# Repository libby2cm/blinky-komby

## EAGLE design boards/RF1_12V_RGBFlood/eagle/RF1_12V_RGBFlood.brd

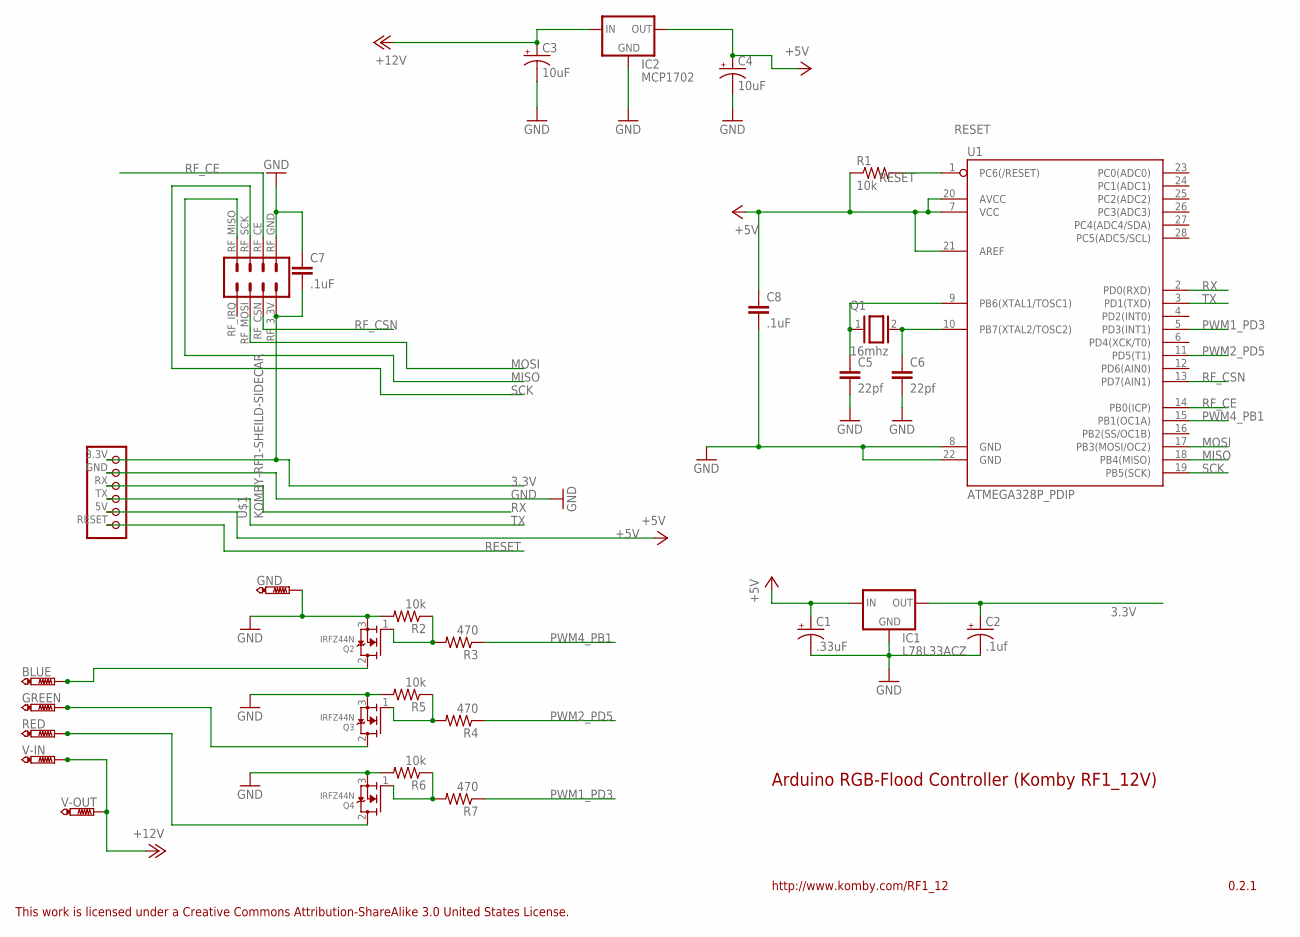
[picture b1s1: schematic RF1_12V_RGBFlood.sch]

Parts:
BLUE: PTR1PAD1-13Y; P1-13Y
C1: .33uF; E1,8-4
C2: .1uf; E1,8-4
C3, C4: 10uF; E1,8-4
C5, C6: 22pf; C025-024X044
C7, C8: .1uF; C025-024X044
GND: PTR1PAD1-13Y; P1-13Y
GREEN: PTR1PAD1-13Y; P1-13Y
IC1: L78L33ACZ; 78LXX
IC2: MCP1702; TO92
Q1: 16mhz; QS
Q2, Q3, Q4: IRFZ44N; TO220V
R1, R2, R5, R6: 10k; 0207/7
R3, R4, R7: 470; 0207/7
RED: PTR1PAD1-13Y; P1-13Y
U1: ATMEGA328P_PDIP; DIL28-3
U$1: KOMBY-RF1-SHEILD-SIDECAR; KOMBY-RF1-SIDECAR
V-IN: PTR1PAD1-13Y; P1-13Y
V-OUT: PTR1PAD1-13Y; P1-13Y

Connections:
3.3V: C2.+, C7.2, IC1.OUT, U$1.3.3V, U$1.RF_3.3V
+5V: C1.+, C4.+, C8.1, IC1.IN, IC2.3 (OUT), R1.1, U1.7 (VCC), U1.20 (AVCC), U1.21 (AREF), U$1.5V
+12V: C3.+, IC2.2 (IN), V-IN.TP, V-OUT.TP
GND: C1.-, C2.-, C3.-, C4.-, C5.2, C6.2, C7.1, C8.2, GND.TP, IC1.GND, IC2.1 (GND), Q2.3 (S), Q3.3 (S), Q4.3 (S), R2.2, R5.2, R6.2, U1.8 (GND), U1.22 (GND), U$1.GND, U$1.RF_GND (RFGND_1)
MISO: U1.18 (PB4(MISO)), U$1.RF_MISO
MOSI: U1.17 (PB3(MOSI/OC2)), U$1.RF_MOSI
unnamed: C6.1, Q1.2, U1.10 (PB7(XTAL2/TOSC2))
unnamed: C5.1, Q1.1, U1.9 (PB6(XTAL1/TOSC1))
PWM1_PD3: R7.1, U1.5 (PD3(INT1))
PWM2_PD5: R4.1, U1.11 (PD5(T1))
PWM4_PB1: R3.1, U1.15 (PB1(OC1A))
RESET: R1.2, U1.1 (PC6(/RESET)), U$1.RESET
RF_CE: U1.14 (PB0(ICP)), U$1.RF_CE
RF_CSN: U1.13 (PD7(AIN1)), U$1.RF_CSN
RGB_N$1: Q2.1 (G), R2.1, R3.2
RGB_N$2: Q3.1 (G), R4.2, R5.1
RGB_N$3: Q4.1 (G), R6.1, R7.2
RGB_N$4: Q4.2 (D), RED.TP
RGB_N$7: GREEN.TP, Q3.2 (D)
RGB_N$8: BLUE.TP, Q2.2 (D)
RX: U1.2 (PD0(RXD)), U$1.RX
SCK: U1.19 (PB5(SCK)), U$1.RF_SCK
TX: U1.3 (PD1(TXD)), U$1.TX

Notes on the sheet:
Arduino RGB-Flood Controller (Komby RF1_12V)
0.2.1
http://www.komby.com/RF1_12
This work is licensed under a Creative Commons Attribution-ShareAlike 3.0 United States License.

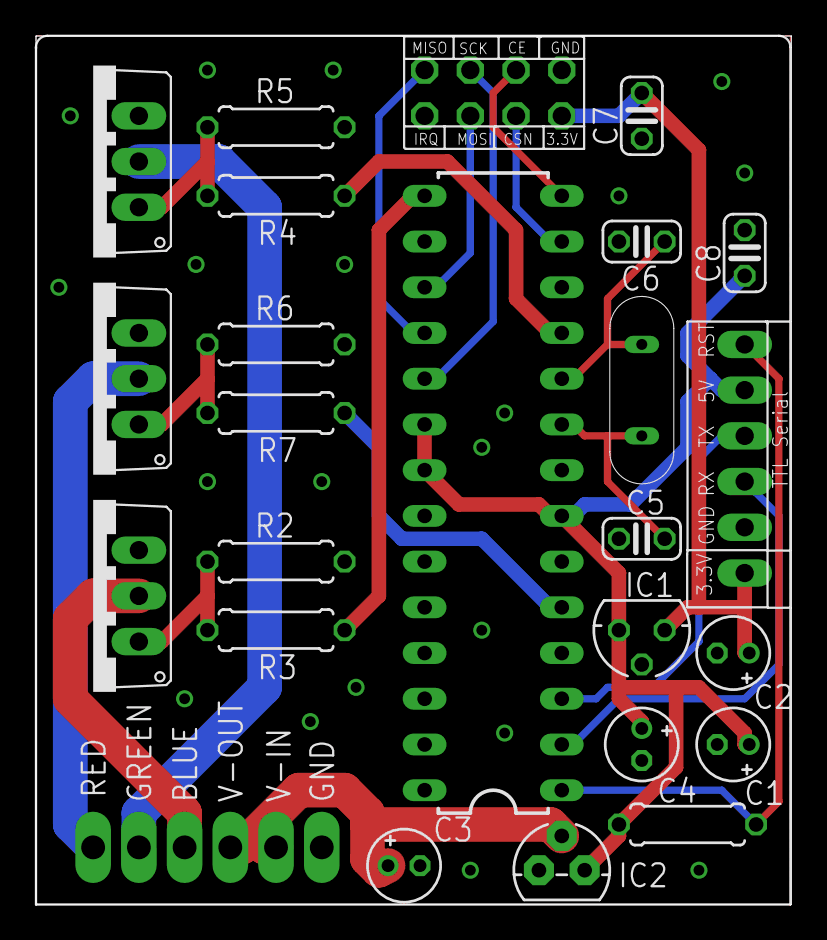
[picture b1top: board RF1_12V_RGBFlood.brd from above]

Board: 2 copper layers, 42.0 x 48.2 mm, 29 parts (0 on the bottom side), 23 nets.

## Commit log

2016-11-28 :confetti_ball: Added .gitattributes
2016-11-28 initial

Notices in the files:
parts and their libraries:
SparkFun-DigitalIC: Licensing: CC v3.0 Share-Alike You are welcome to use this library for commercial purposes.
